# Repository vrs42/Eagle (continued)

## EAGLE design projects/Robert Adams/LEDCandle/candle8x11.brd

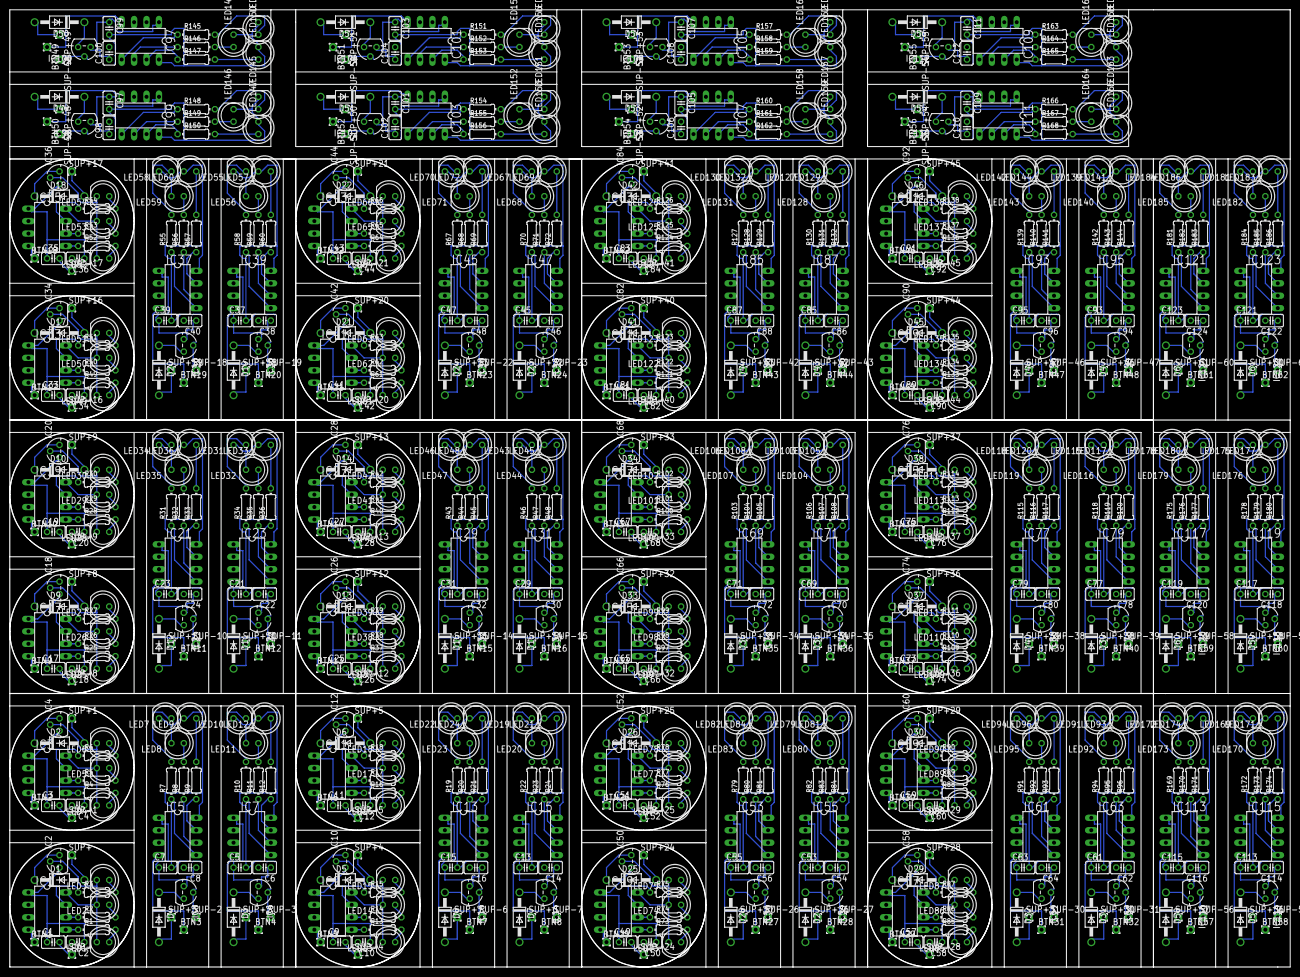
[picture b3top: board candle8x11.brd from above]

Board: 2 copper layers, 261.6 x 195.6 mm, 868 parts (0 on the bottom side), 596 nets.

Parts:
BTN1, BTN2, BTN3, BTN4, BTN5, BTN6, BTN7, BTN8, BTN9, BTN10, BTN11, BTN12, BTN13, BTN14, BTN15, BTN16, BTN17, BTN18, BTN19, BTN20, BTN21, BTN22, BTN23, BTN24, BTN25, BTN26, BTN27, BTN28, BTN29, BTN30, BTN31, BTN32, BTN33, BTN34, BTN35, BTN36, BTN37, BTN38, BTN39, BTN40, BTN41, BTN42, BTN43, BTN44, BTN45, BTN46, BTN47, BTN48, BTN49, BTN50, BTN51, BTN52, BTN53, BTN54, BTN55, BTN56, BTN57, BTN58, BTN59, BTN60, BTN61, BTN62: 1,6/0,8
C1, C2, C3, C4, C5, C6, C7, C8, C9, C10, C11, C12, C13, C14, C15, C16, C17, C18, C19, C20, C21, C22, C23, C24, C25, C26, C27, C28, C29, C30, C31, C32, C33, C34, C35, C36, C37, C38, C39, C40, C41, C42, C43, C44, C45, C46, C47, C48, C49, C50, C51, C52, C53, C54, C55, C56, C57, C58, C59, C60, C61, C62, C63, C64, C65, C66, C67, C68, C69, C70, C71, C72, C73, C74, C75, C76, C77, C78, C79, C80, C81, C82, C83, C84, C85, C86, C87, C88, C89, C90, C91, C92, C93, C94, C95, C96, C97, C98, C99, C100, C101, C102, C103, C104, C105, C106, C107, C108, C109, C110, C111, C112, C113, C114, C115, C116, C117, C118, C119, C120, C121, C122, C123, C124: C025-025X050
D1, D2, D3, D4, D5, D6, D7, D8, D9, D10, D11, D12, D13, D14, D15, D16, D17, D18, D19, D20, D21, D22, D23, D24, D25, D26, D27, D28, D29, D30, D31, D32, D33, D34, D35, D36, D37, D38, D39, D40, D41, D42, D43, D44, D45, D46, D47, D48, D49, D50, D51, D52, D53, D54, D55, D56, D57, D58, D59, D60, D61, D62: 1N4004; DO41-10
IC1, IC3, IC5, IC7, IC9, IC11, IC13, IC15, IC17, IC19, IC21, IC23, IC25, IC27, IC29, IC31, IC33, IC35, IC37, IC39, IC41, IC43, IC45, IC47, IC49, IC51, IC53, IC55, IC57, IC59, IC61, IC63, IC65, IC67, IC69, IC71, IC73, IC75, IC77, IC79, IC81, IC83, IC85, IC87, IC89, IC91, IC93, IC95, IC97, IC99, IC101, IC103, IC105, IC107, IC109, IC111, IC113, IC115, IC117, IC119, IC121, IC123: PIC12F629P; DIL8
IC2, IC4, IC6, IC8, IC10, IC12, IC14, IC16, IC18, IC20, IC22, IC24, IC26, IC28, IC30, IC32, IC34, IC36, IC38, IC40, IC42, IC44, IC46, IC48, IC50, IC52, IC54, IC56, IC58, IC60, IC62, IC64, IC66, IC68, IC70, IC72, IC74, IC76, IC78, IC80, IC82, IC84, IC86, IC88, IC90, IC92, IC94, IC96, IC98, IC100, IC102, IC104, IC106, IC108, IC110, IC112, IC114, IC116, IC118, IC120, IC122, IC124: 7805L; TO92
LED1, LED2, LED3, LED4, LED5, LED6, LED7, LED8, LED9, LED10, LED11, LED12, LED13, LED14, LED15, LED16, LED17, LED18, LED19, LED20, LED21, LED22, LED23, LED24, LED25, LED26, LED27, LED28, LED29, LED30, LED31, LED32, LED33, LED34, LED35, LED36, LED37, LED38, LED39, LED40, LED41, LED42, LED43, LED44, LED45, LED46, LED47, LED48, LED49, LED50, LED51, LED52, LED53, LED54, LED55, LED56, LED57, LED58, LED59, LED60, LED61, LED62, LED63, LED64, LED65, LED66, LED67, LED68, LED69, LED70, LED71, LED72, LED73, LED74, LED75, LED76, LED77, LED78, LED79, LED80, LED81, LED82, LED83, LED84, LED85, LED86, LED87, LED88, LED89, LED90, LED91, LED92, LED93, LED94, LED95, LED96, LED97, LED98, LED99, LED100, LED101, LED102, LED103, LED104, LED105, LED106, LED107, LED108, LED109, LED110, LED111, LED112, LED113, LED114, LED115, LED116, LED117, LED118, LED119, LED120, LED121, LED122, LED123, LED124, LED125, LED126, LED127, LED128, LED129, LED130, LED131, LED132, LED133, LED134, LED135, LED136, LED137, LED138, LED139, LED140, LED141, LED142, LED143, LED144, LED145, LED146, LED147, LED148, LED149, LED150, LED151, LED152, LED153, LED154, LED155, LED156, LED157, LED158, LED159, LED160, LED161, LED162, LED163, LED164, LED165, LED166, LED167, LED168, LED169, LED170, LED171, LED172, LED173, LED174, LED175, LED176, LED177, LED178, LED179, LED180, LED181, LED182, LED183, LED184, LED185, LED186: LED5MM
R1, R2, R3, R4, R5, R6, R7, R8, R9, R10, R11, R12, R13, R14, R15, R16, R17, R18, R19, R20, R21, R22, R23, R24, R25, R26, R27, R28, R29, R30, R31, R32, R33, R34, R35, R36, R37, R38, R39, R40, R41, R42, R43, R44, R45, R46, R47, R48, R49, R50, R51, R52, R53, R54, R55, R56, R57, R58, R59, R60, R61, R62, R63, R64, R65, R66, R67, R68, R69, R70, R71, R72, R73, R74, R75, R76, R77, R78, R79, R80, R81, R82, R83, R84, R85, R86, R87, R88, R89, R90, R91, R92, R93, R94, R95, R96, R97, R98, R99, R100, R101, R102, R103, R104, R105, R106, R107, R108, R109, R110, R111, R112, R113, R114, R115, R116, R117, R118, R119, R120, R121, R122, R123, R124, R125, R126, R127, R128, R129, R130, R131, R132, R133, R134, R135, R136, R137, R138, R139, R140, R141, R142, R143, R144, R145, R146, R147, R148, R149, R150, R151, R152, R153, R154, R155, R156, R157, R158, R159, R160, R161, R162, R163, R164, R165, R166, R167, R168, R169, R170, R171, R172, R173, R174, R175, R176, R177, R178, R179, R180, R181, R182, R183, R184, R185, R186: 0204/7
SUP+, SUP+1, SUP+2, SUP+3, SUP+4, SUP+5, SUP+6, SUP+7, SUP+8, SUP+9, SUP+10, SUP+11, SUP+12, SUP+13, SUP+14, SUP+15, SUP+16, SUP+17, SUP+18, SUP+19, SUP+20, SUP+21, SUP+22, SUP+23, SUP+24, SUP+25, SUP+26, SUP+27, SUP+28, SUP+29, SUP+30, SUP+31, SUP+32, SUP+33, SUP+34, SUP+35, SUP+36, SUP+37, SUP+38, SUP+39, SUP+40, SUP+41, SUP+42, SUP+43, SUP+44, SUP+45, SUP+46, SUP+47, SUP+48, SUP+49, SUP+50, SUP+51, SUP+52, SUP+53, SUP+54, SUP+55, SUP+56, SUP+57, SUP+58, SUP+59, SUP+60, SUP+61: 1,6/0,8
SUP-, SUP-1, SUP-2, SUP-3, SUP-4, SUP-5, SUP-6, SUP-7, SUP-8, SUP-9, SUP-10, SUP-11, SUP-12, SUP-13, SUP-14, SUP-15, SUP-16, SUP-17, SUP-18, SUP-19, SUP-20, SUP-21, SUP-22, SUP-23, SUP-24, SUP-25, SUP-26, SUP-27, SUP-28, SUP-29, SUP-30, SUP-31, SUP-32, SUP-33, SUP-34, SUP-35, SUP-36, SUP-37, SUP-38, SUP-39, SUP-40, SUP-41, SUP-42, SUP-43, SUP-44, SUP-45, SUP-46, SUP-47, SUP-48, SUP-49, SUP-50, SUP-51, SUP-52, SUP-53, SUP-54, SUP-55, SUP-56, SUP-57, SUP-58, SUP-59, SUP-60, SUP-61: 1,6/0,8

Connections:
GND: C1.2, C2.2, C3.2, C4.2, C5.2, C6.2, C7.2, C8.2, IC1.8, IC2.2, IC3.8, IC4.2, IC5.8, IC6.2, IC7.8, IC8.2, LED1.K, LED2.K, LED3.K, LED4.K, LED5.K, LED6.K, LED7.K, LED8.K, LED9.K, LED10.K, LED11.K, LED12.K, SUP-.1, SUP-1.1, SUP-2.1, SUP-3.1
GND1: C9.2, C10.2, C11.2, C12.2, C13.2, C14.2, C15.2, C16.2, IC9.8, IC10.2, IC11.8, IC12.2, IC13.8, IC14.2, IC15.8, IC16.2, LED13.K, LED14.K, LED15.K, LED16.K, LED17.K, LED18.K, LED19.K, LED20.K, LED21.K, LED22.K, LED23.K, LED24.K, SUP-4.1, SUP-5.1, SUP-6.1, SUP-7.1
GND2: C17.2, C18.2, C19.2, C20.2, C21.2, C22.2, C23.2, C24.2, IC17.8, IC18.2, IC19.8, IC20.2, IC21.8, IC22.2, IC23.8, IC24.2, LED25.K, LED26.K, LED27.K, LED28.K, LED29.K, LED30.K, LED31.K, LED32.K, LED33.K, LED34.K, LED35.K, LED36.K, SUP-8.1, SUP-9.1, SUP-10.1, SUP-11.1
GND3: C25.2, C26.2, C27.2, C28.2, C29.2, C30.2, C31.2, C32.2, IC25.8, IC26.2, IC27.8, IC28.2, IC29.8, IC30.2, IC31.8, IC32.2, LED37.K, LED38.K, LED39.K, LED40.K, LED41.K, LED42.K, LED43.K, LED44.K, LED45.K, LED46.K, LED47.K, LED48.K, SUP-12.1, SUP-13.1, SUP-14.1, SUP-15.1
GND4: C33.2, C34.2, C35.2, C36.2, C37.2, C38.2, C39.2, C40.2, IC33.8, IC34.2, IC35.8, IC36.2, IC37.8, IC38.2, IC39.8, IC40.2, LED49.K, LED50.K, LED51.K, LED52.K, LED53.K, LED54.K, LED55.K, LED56.K, LED57.K, LED58.K, LED59.K, LED60.K, SUP-16.1, SUP-17.1, SUP-18.1, SUP-19.1
GND5: C41.2, C42.2, C43.2, C44.2, C45.2, C46.2, C47.2, C48.2, IC41.8, IC42.2, IC43.8, IC44.2, IC45.8, IC46.2, IC47.8, IC48.2, LED61.K, LED62.K, LED63.K, LED64.K, LED65.K, LED66.K, LED67.K, LED68.K, LED69.K, LED70.K, LED71.K, LED72.K, SUP-20.1, SUP-21.1, SUP-22.1, SUP-23.1
GND6: C49.2, C50.2, C51.2, C52.2, C53.2, C54.2, C55.2, C56.2, IC49.8, IC50.2, IC51.8, IC52.2, IC53.8, IC54.2, IC55.8, IC56.2, LED73.K, LED74.K, LED75.K, LED76.K, LED77.K, LED78.K, LED79.K, LED80.K, LED81.K, LED82.K, LED83.K, LED84.K, SUP-24.1, SUP-25.1, SUP-26.1, SUP-27.1
GND7: C57.2, C58.2, C59.2, C60.2, C61.2, C62.2, C63.2, C64.2, IC57.8, IC58.2, IC59.8, IC60.2, IC61.8, IC62.2, IC63.8, IC64.2, LED85.K, LED86.K, LED87.K, LED88.K, LED89.K, LED90.K, LED91.K, LED92.K, LED93.K, LED94.K, LED95.K, LED96.K, SUP-28.1, SUP-29.1, SUP-30.1, SUP-31.1
GND8: C65.2, C66.2, C67.2, C68.2, C69.2, C70.2, C71.2, C72.2, IC65.8, IC66.2, IC67.8, IC68.2, IC69.8, IC70.2, IC71.8, IC72.2, LED97.K, LED98.K, LED99.K, LED100.K, LED101.K, LED102.K, LED103.K, LED104.K, LED105.K, LED106.K, LED107.K, LED108.K, SUP-32.1, SUP-33.1, SUP-34.1, SUP-35.1
GND9: C73.2, C74.2, C75.2, C76.2, C77.2, C78.2, C79.2, C80.2, IC73.8, IC74.2, IC75.8, IC76.2, IC77.8, IC78.2, IC79.8, IC80.2, LED109.K, LED110.K, LED111.K, LED112.K, LED113.K, LED114.K, LED115.K, LED116.K, LED117.K, LED118.K, LED119.K, LED120.K, SUP-36.1, SUP-37.1, SUP-38.1, SUP-39.1
GND10: C81.2, C82.2, C83.2, C84.2, C85.2, C86.2, C87.2, C88.2, IC81.8, IC82.2, IC83.8, IC84.2, IC85.8, IC86.2, IC87.8, IC88.2, LED121.K, LED122.K, LED123.K, LED124.K, LED125.K, LED126.K, LED127.K, LED128.K, LED129.K, LED130.K, LED131.K, LED132.K, SUP-40.1, SUP-41.1, SUP-42.1, SUP-43.1
GND11: C89.2, C90.2, C91.2, C92.2, C93.2, C94.2, C95.2, C96.2, IC89.8, IC90.2, IC91.8, IC92.2, IC93.8, IC94.2, IC95.8, IC96.2, LED133.K, LED134.K, LED135.K, LED136.K, LED137.K, LED138.K, LED139.K, LED140.K, LED141.K, LED142.K, LED143.K, LED144.K, SUP-44.1, SUP-45.1, SUP-46.1, SUP-47.1
GND12: C97.2, C98.2, C99.2, C100.2, IC97.8, IC98.2, IC99.8, IC100.2, LED145.K, LED146.K, LED147.K, LED148.K, LED149.K, LED150.K, SUP-48.1, SUP-49.1
GND13: C101.2, C102.2, C103.2, C104.2, IC101.8, IC102.2, IC103.8, IC104.2, LED151.K, LED152.K, LED153.K, LED154.K, LED155.K, LED156.K, SUP-50.1, SUP-51.1
GND14: C105.2, C106.2, C107.2, C108.2, IC105.8, IC106.2, IC107.8, IC108.2, LED157.K, LED158.K, LED159.K, LED160.K, LED161.K, LED162.K, SUP-52.1, SUP-53.1
GND15: C109.2, C110.2, C111.2, C112.2, IC109.8, IC110.2, IC111.8, IC112.2, LED163.K, LED164.K, LED165.K, LED166.K, LED167.K, LED168.K, SUP-54.1, SUP-55.1
GND16: C113.2, C114.2, C115.2, C116.2, IC113.8, IC114.2, IC115.8, IC116.2, LED169.K, LED170.K, LED171.K, LED172.K, LED173.K, LED174.K, SUP-56.1, SUP-57.1
GND17: C117.2, C118.2, C119.2, C120.2, IC117.8, IC118.2, IC119.8, IC120.2, LED175.K, LED176.K, LED177.K, LED178.K, LED179.K, LED180.K, SUP-58.1, SUP-59.1
GND18: C121.2, C122.2, C123.2, C124.2, IC121.8, IC122.2, IC123.8, IC124.2, LED181.K, LED182.K, LED183.K, LED184.K, LED185.K, LED186.K, SUP-60.1, SUP-61.1
unnamed: IC3.7, R6.1
unnamed: BTN1.1, IC1.4
unnamed: IC1.7, R3.1
unnamed: IC1.6, R2.1
unnamed: IC1.5, R1.1
unnamed: LED1.A, R1.2
unnamed: LED2.A, R2.2
unnamed: LED3.A, R3.2
unnamed: IC3.6, R5.1
unnamed: D1.C, IC2.3
unnamed: IC3.5, R4.1
unnamed: LED4.A, R4.2
unnamed: LED5.A, R5.2
unnamed: LED6.A, R6.2
unnamed: D2.C, IC4.3
unnamed: BTN2.1, IC3.4
unnamed: IC5.7, R9.1
unnamed: IC5.6, R8.1
unnamed: IC5.5, R7.1
unnamed: LED7.A, R7.2
unnamed: LED8.A, R8.2
unnamed: D3.C, IC6.3
unnamed: BTN3.1, IC5.4
unnamed: IC7.7, R12.1
unnamed: IC7.6, R11.1
unnamed: IC7.5, R10.1
unnamed: LED9.A, R9.2
unnamed: LED10.A, R10.2
unnamed: LED11.A, R11.2
unnamed: D4.C, IC8.3
unnamed: BTN4.1, IC7.4
unnamed: D1.A, SUP+.1
unnamed: LED12.A, R12.2
unnamed: D3.A, SUP+2.1
unnamed: D4.A, SUP+3.1
unnamed: D2.A, SUP+1.1
unnamed: IC9.7, R15.1
unnamed: IC9.6, R14.1
unnamed: IC9.5, R13.1
unnamed: D5.C, IC10.3
unnamed: BTN5.1, IC9.4
unnamed: IC11.7, R18.1
unnamed: IC11.6, R17.1
unnamed: IC11.5, R16.1
unnamed: D6.C, IC12.3
unnamed: BTN6.1, IC11.4
unnamed: IC13.7, R21.1
unnamed: IC13.6, R20.1
unnamed: IC13.5, R19.1
unnamed: D7.C, IC14.3
unnamed: BTN7.1, IC13.4
unnamed: IC15.7, R24.1
unnamed: IC15.6, R23.1
unnamed: IC15.5, R22.1
unnamed: D8.C, IC16.3
unnamed: BTN8.1, IC15.4
unnamed: D5.A, SUP+4.1
unnamed: LED13.A, R13.2
unnamed: LED14.A, R14.2
unnamed: LED15.A, R15.2
unnamed: LED16.A, R16.2
unnamed: LED17.A, R17.2
unnamed: LED18.A, R18.2
unnamed: LED19.A, R22.2
unnamed: LED20.A, R23.2
unnamed: LED21.A, R24.2
unnamed: LED22.A, R19.2
unnamed: LED23.A, R20.2
unnamed: LED24.A, R21.2
unnamed: D7.A, SUP+6.1
unnamed: D8.A, SUP+7.1
unnamed: D6.A, SUP+5.1
unnamed: IC17.7, R27.1
unnamed: IC17.6, R26.1
unnamed: IC17.5, R25.1
unnamed: D9.C, IC18.3
unnamed: BTN9.1, IC17.4
unnamed: IC19.7, R30.1
unnamed: IC19.6, R29.1
unnamed: IC19.5, R28.1
unnamed: D10.C, IC20.3
unnamed: BTN10.1, IC19.4
unnamed: IC21.7, R33.1
unnamed: IC21.6, R32.1
unnamed: IC21.5, R31.1
unnamed: D11.C, IC22.3
unnamed: BTN11.1, IC21.4
unnamed: IC23.7, R36.1
unnamed: IC23.6, R35.1
unnamed: IC23.5, R34.1
unnamed: D12.C, IC24.3
unnamed: BTN12.1, IC23.4
unnamed: D9.A, SUP+8.1
unnamed: LED25.A, R25.2
unnamed: LED26.A, R26.2
unnamed: LED27.A, R27.2
unnamed: LED28.A, R28.2
unnamed: LED29.A, R29.2
unnamed: LED30.A, R30.2
unnamed: LED31.A, R34.2
unnamed: LED32.A, R35.2
unnamed: LED33.A, R36.2
unnamed: LED34.A, R31.2
unnamed: LED35.A, R32.2
unnamed: LED36.A, R33.2
unnamed: D11.A, SUP+10.1
unnamed: D12.A, SUP+11.1
unnamed: D10.A, SUP+9.1
unnamed: IC25.7, R39.1
unnamed: IC25.6, R38.1
unnamed: IC25.5, R37.1
unnamed: D13.C, IC26.3
unnamed: BTN13.1, IC25.4
unnamed: IC27.7, R42.1
unnamed: IC27.6, R41.1
unnamed: IC27.5, R40.1
unnamed: D14.C, IC28.3
unnamed: BTN14.1, IC27.4
unnamed: IC29.7, R45.1
unnamed: IC29.6, R44.1
unnamed: IC29.5, R43.1
unnamed: D15.C, IC30.3
unnamed: BTN15.1, IC29.4
unnamed: IC31.7, R48.1
unnamed: IC31.6, R47.1
unnamed: IC31.5, R46.1
unnamed: D16.C, IC32.3
unnamed: BTN16.1, IC31.4
unnamed: D13.A, SUP+12.1
unnamed: LED37.A, R37.2
unnamed: LED38.A, R38.2
unnamed: LED39.A, R39.2
unnamed: LED40.A, R40.2
unnamed: LED41.A, R41.2
unnamed: LED42.A, R42.2
unnamed: LED43.A, R46.2
unnamed: LED44.A, R47.2
unnamed: LED45.A, R48.2
unnamed: LED46.A, R43.2
unnamed: LED47.A, R44.2
unnamed: LED48.A, R45.2
unnamed: D15.A, SUP+14.1
unnamed: D16.A, SUP+15.1
unnamed: D14.A, SUP+13.1
unnamed: IC33.7, R51.1
unnamed: IC33.6, R50.1
unnamed: IC33.5, R49.1
unnamed: D17.C, IC34.3
unnamed: BTN17.1, IC33.4
unnamed: IC35.7, R54.1
unnamed: IC35.6, R53.1
unnamed: IC35.5, R52.1
unnamed: D18.C, IC36.3
unnamed: BTN18.1, IC35.4
unnamed: IC37.7, R57.1
unnamed: IC37.6, R56.1
unnamed: IC37.5, R55.1
unnamed: D19.C, IC38.3
unnamed: BTN19.1, IC37.4
unnamed: IC39.7, R60.1
unnamed: IC39.6, R59.1
unnamed: IC39.5, R58.1
unnamed: D20.C, IC40.3
unnamed: BTN20.1, IC39.4
unnamed: D17.A, SUP+16.1
unnamed: LED49.A, R49.2
unnamed: LED50.A, R50.2
unnamed: LED51.A, R51.2
unnamed: LED52.A, R52.2
unnamed: LED53.A, R53.2
unnamed: LED54.A, R54.2
unnamed: LED55.A, R58.2
unnamed: LED56.A, R59.2
unnamed: LED57.A, R60.2
unnamed: LED58.A, R55.2
unnamed: LED59.A, R56.2
unnamed: LED60.A, R57.2
unnamed: D19.A, SUP+18.1
unnamed: D20.A, SUP+19.1
unnamed: D18.A, SUP+17.1
unnamed: IC41.7, R63.1
unnamed: IC41.6, R62.1
unnamed: IC41.5, R61.1
unnamed: D21.C, IC42.3
unnamed: BTN21.1, IC41.4
unnamed: IC43.7, R66.1
unnamed: IC43.6, R65.1
unnamed: IC43.5, R64.1
unnamed: D22.C, IC44.3
unnamed: BTN22.1, IC43.4
unnamed: IC45.7, R69.1
unnamed: IC45.6, R68.1
unnamed: IC45.5, R67.1
unnamed: D23.C, IC46.3
unnamed: BTN23.1, IC45.4
unnamed: IC47.7, R72.1
unnamed: IC47.6, R71.1
unnamed: IC47.5, R70.1
unnamed: D24.C, IC48.3
unnamed: BTN24.1, IC47.4
unnamed: D21.A, SUP+20.1
unnamed: LED61.A, R61.2
unnamed: LED62.A, R62.2
unnamed: LED63.A, R63.2
unnamed: LED64.A, R64.2
unnamed: LED65.A, R65.2
unnamed: LED66.A, R66.2
unnamed: LED67.A, R70.2
unnamed: LED68.A, R71.2
unnamed: LED69.A, R72.2
unnamed: LED70.A, R67.2
unnamed: LED71.A, R68.2
unnamed: LED72.A, R69.2
unnamed: D23.A, SUP+22.1
unnamed: D24.A, SUP+23.1
unnamed: D22.A, SUP+21.1
unnamed: IC49.7, R75.1
unnamed: IC49.6, R74.1
unnamed: IC49.5, R73.1
unnamed: D25.C, IC50.3
unnamed: BTN25.1, IC49.4
unnamed: IC51.7, R78.1
unnamed: IC51.6, R77.1
unnamed: IC51.5, R76.1
unnamed: D26.C, IC52.3
unnamed: BTN26.1, IC51.4
unnamed: IC53.7, R81.1
unnamed: IC53.6, R80.1
unnamed: IC53.5, R79.1
unnamed: D27.C, IC54.3
unnamed: BTN27.1, IC53.4
unnamed: IC55.7, R84.1
unnamed: IC55.6, R83.1
unnamed: IC55.5, R82.1
unnamed: D28.C, IC56.3
unnamed: BTN28.1, IC55.4
unnamed: D25.A, SUP+24.1
unnamed: LED73.A, R73.2
unnamed: LED74.A, R74.2
unnamed: LED75.A, R75.2
unnamed: LED76.A, R76.2
unnamed: LED77.A, R77.2
unnamed: LED78.A, R78.2
unnamed: LED79.A, R82.2
unnamed: LED80.A, R83.2
unnamed: LED81.A, R84.2
unnamed: LED82.A, R79.2
unnamed: LED83.A, R80.2
unnamed: LED84.A, R81.2
unnamed: D27.A, SUP+26.1
unnamed: D28.A, SUP+27.1
unnamed: D26.A, SUP+25.1
unnamed: IC57.7, R87.1
unnamed: IC57.6, R86.1
unnamed: IC57.5, R85.1
unnamed: D29.C, IC58.3
unnamed: BTN29.1, IC57.4
unnamed: IC59.7, R90.1
unnamed: IC59.6, R89.1
unnamed: IC59.5, R88.1
unnamed: D30.C, IC60.3
unnamed: BTN30.1, IC59.4
unnamed: IC61.7, R93.1
unnamed: IC61.6, R92.1
unnamed: IC61.5, R91.1
unnamed: D31.C, IC62.3
unnamed: BTN31.1, IC61.4
unnamed: IC63.7, R96.1
unnamed: IC63.6, R95.1
unnamed: IC63.5, R94.1
unnamed: D32.C, IC64.3
unnamed: BTN32.1, IC63.4
unnamed: D29.A, SUP+28.1
unnamed: LED85.A, R85.2
unnamed: LED86.A, R86.2
unnamed: LED87.A, R87.2
unnamed: LED88.A, R88.2
unnamed: LED89.A, R89.2
unnamed: LED90.A, R90.2
unnamed: LED91.A, R94.2
unnamed: LED92.A, R95.2
unnamed: LED93.A, R96.2
unnamed: LED94.A, R91.2
unnamed: LED95.A, R92.2
unnamed: LED96.A, R93.2
unnamed: D31.A, SUP+30.1
unnamed: D32.A, SUP+31.1
unnamed: D30.A, SUP+29.1
unnamed: IC65.7, R99.1
unnamed: IC65.6, R98.1
unnamed: IC65.5, R97.1
unnamed: D33.C, IC66.3
unnamed: BTN33.1, IC65.4
unnamed: IC67.7, R102.1
unnamed: IC67.6, R101.1
unnamed: IC67.5, R100.1
unnamed: D34.C, IC68.3
unnamed: BTN34.1, IC67.4
unnamed: IC69.7, R105.1
unnamed: IC69.6, R104.1
unnamed: IC69.5, R103.1
unnamed: D35.C, IC70.3
unnamed: BTN35.1, IC69.4
unnamed: IC71.7, R108.1
unnamed: IC71.6, R107.1
unnamed: IC71.5, R106.1
unnamed: D36.C, IC72.3
unnamed: BTN36.1, IC71.4
unnamed: D33.A, SUP+32.1
unnamed: LED97.A, R97.2
unnamed: LED98.A, R98.2
unnamed: LED99.A, R99.2
unnamed: LED100.A, R100.2
unnamed: LED101.A, R101.2
unnamed: LED102.A, R102.2
unnamed: LED103.A, R106.2
unnamed: LED104.A, R107.2
unnamed: LED105.A, R108.2
unnamed: LED106.A, R103.2
unnamed: LED107.A, R104.2
unnamed: LED108.A, R105.2
unnamed: D35.A, SUP+34.1
unnamed: D36.A, SUP+35.1
unnamed: D34.A, SUP+33.1
unnamed: IC73.7, R111.1
unnamed: IC73.6, R110.1
unnamed: IC73.5, R109.1
unnamed: D37.C, IC74.3
unnamed: BTN37.1, IC73.4
unnamed: IC75.7, R114.1
unnamed: IC75.6, R113.1
unnamed: IC75.5, R112.1
unnamed: D38.C, IC76.3
unnamed: BTN38.1, IC75.4
unnamed: IC77.7, R117.1
unnamed: IC77.6, R116.1
unnamed: IC77.5, R115.1
unnamed: D39.C, IC78.3
unnamed: BTN39.1, IC77.4
unnamed: IC79.7, R120.1
unnamed: IC79.6, R119.1
unnamed: IC79.5, R118.1
unnamed: D40.C, IC80.3
unnamed: BTN40.1, IC79.4
unnamed: D37.A, SUP+36.1
unnamed: LED109.A, R109.2
unnamed: LED110.A, R110.2
unnamed: LED111.A, R111.2
unnamed: LED112.A, R112.2
unnamed: LED113.A, R113.2
unnamed: LED114.A, R114.2
unnamed: LED115.A, R118.2
unnamed: LED116.A, R119.2
unnamed: LED117.A, R120.2
unnamed: LED118.A, R115.2
unnamed: LED119.A, R116.2
unnamed: LED120.A, R117.2
unnamed: D39.A, SUP+38.1
unnamed: D40.A, SUP+39.1
unnamed: D38.A, SUP+37.1
unnamed: IC81.7, R123.1
unnamed: IC81.6, R122.1
unnamed: IC81.5, R121.1
unnamed: D41.C, IC82.3
unnamed: BTN41.1, IC81.4
unnamed: IC83.7, R126.1
unnamed: IC83.6, R125.1
unnamed: IC83.5, R124.1
unnamed: D42.C, IC84.3
unnamed: BTN42.1, IC83.4
unnamed: IC85.7, R129.1
unnamed: IC85.6, R128.1
unnamed: IC85.5, R127.1
unnamed: D43.C, IC86.3
unnamed: BTN43.1, IC85.4
unnamed: IC87.7, R132.1
unnamed: IC87.6, R131.1
unnamed: IC87.5, R130.1
unnamed: D44.C, IC88.3
unnamed: BTN44.1, IC87.4
unnamed: D41.A, SUP+40.1
unnamed: LED121.A, R121.2
unnamed: LED122.A, R122.2
unnamed: LED123.A, R123.2
unnamed: LED124.A, R124.2
unnamed: LED125.A, R125.2
unnamed: LED126.A, R126.2
unnamed: LED127.A, R130.2
unnamed: LED128.A, R131.2
unnamed: LED129.A, R132.2
unnamed: LED130.A, R127.2
unnamed: LED131.A, R128.2
unnamed: LED132.A, R129.2
unnamed: D43.A, SUP+42.1
unnamed: D44.A, SUP+43.1
unnamed: D42.A, SUP+41.1
unnamed: IC89.7, R135.1
unnamed: IC89.6, R134.1
unnamed: IC89.5, R133.1
unnamed: D45.C, IC90.3
unnamed: BTN45.1, IC89.4
unnamed: IC91.7, R138.1
unnamed: IC91.6, R137.1
unnamed: IC91.5, R136.1
unnamed: D46.C, IC92.3
unnamed: BTN46.1, IC91.4
unnamed: IC93.7, R141.1
unnamed: IC93.6, R140.1
unnamed: IC93.5, R139.1
unnamed: D47.C, IC94.3
unnamed: BTN47.1, IC93.4
unnamed: IC95.7, R144.1
unnamed: IC95.6, R143.1
unnamed: IC95.5, R142.1
unnamed: D48.C, IC96.3
unnamed: BTN48.1, IC95.4
unnamed: D45.A, SUP+44.1
unnamed: LED133.A, R133.2
unnamed: LED134.A, R134.2
unnamed: LED135.A, R135.2
unnamed: LED136.A, R136.2
unnamed: LED137.A, R137.2
unnamed: LED138.A, R138.2
unnamed: LED139.A, R142.2
unnamed: LED140.A, R143.2
unnamed: LED141.A, R144.2
unnamed: LED142.A, R139.2
unnamed: LED143.A, R140.2
unnamed: LED144.A, R141.2
unnamed: D47.A, SUP+46.1
unnamed: D48.A, SUP+47.1
unnamed: D46.A, SUP+45.1
unnamed: IC97.7, R147.1
unnamed: IC97.6, R146.1
unnamed: IC97.5, R145.1
unnamed: D49.C, IC98.3
unnamed: BTN49.1, IC97.4
unnamed: IC99.7, R150.1
unnamed: IC99.6, R149.1
unnamed: IC99.5, R148.1
unnamed: D50.C, IC100.3
unnamed: BTN50.1, IC99.4
unnamed: LED145.A, R148.2
unnamed: LED146.A, R149.2
unnamed: LED147.A, R150.2
unnamed: LED148.A, R145.2
unnamed: LED149.A, R146.2
unnamed: LED150.A, R147.2
unnamed: D49.A, SUP+48.1
unnamed: D50.A, SUP+49.1
unnamed: IC101.7, R153.1
unnamed: IC101.6, R152.1
unnamed: IC101.5, R151.1
unnamed: D51.C, IC102.3
unnamed: BTN51.1, IC101.4
unnamed: IC103.7, R156.1
unnamed: IC103.6, R155.1
unnamed: IC103.5, R154.1
unnamed: D52.C, IC104.3
unnamed: BTN52.1, IC103.4
unnamed: LED151.A, R154.2
unnamed: LED152.A, R155.2
unnamed: LED153.A, R156.2
unnamed: LED154.A, R151.2
unnamed: LED155.A, R152.2
unnamed: LED156.A, R153.2
unnamed: D51.A, SUP+50.1
unnamed: D52.A, SUP+51.1
unnamed: IC105.7, R159.1
unnamed: IC105.6, R158.1
unnamed: IC105.5, R157.1
unnamed: D53.C, IC106.3
unnamed: BTN53.1, IC105.4
unnamed: IC107.7, R162.1
unnamed: IC107.6, R161.1
unnamed: IC107.5, R160.1
unnamed: D54.C, IC108.3
unnamed: BTN54.1, IC107.4
unnamed: LED157.A, R160.2
unnamed: LED158.A, R161.2
unnamed: LED159.A, R162.2
unnamed: LED160.A, R157.2
unnamed: LED161.A, R158.2
unnamed: LED162.A, R159.2
unnamed: D53.A, SUP+52.1
unnamed: D54.A, SUP+53.1
unnamed: IC109.7, R165.1
unnamed: IC109.6, R164.1
unnamed: IC109.5, R163.1
unnamed: D55.C, IC110.3
unnamed: BTN55.1, IC109.4
unnamed: IC111.7, R168.1
unnamed: IC111.6, R167.1
unnamed: IC111.5, R166.1
unnamed: D56.C, IC112.3
unnamed: BTN56.1, IC111.4
unnamed: LED163.A, R166.2
unnamed: LED164.A, R167.2
unnamed: LED165.A, R168.2
unnamed: LED166.A, R163.2
unnamed: LED167.A, R164.2
unnamed: LED168.A, R165.2
unnamed: D55.A, SUP+54.1
unnamed: D56.A, SUP+55.1
unnamed: IC113.7, R171.1
unnamed: IC113.6, R170.1
unnamed: IC113.5, R169.1
unnamed: D57.C, IC114.3
unnamed: BTN57.1, IC113.4
unnamed: IC115.7, R174.1
unnamed: IC115.6, R173.1
unnamed: IC115.5, R172.1
unnamed: D58.C, IC116.3
unnamed: BTN58.1, IC115.4
unnamed: LED169.A, R172.2
unnamed: LED170.A, R173.2
unnamed: LED171.A, R174.2
unnamed: LED172.A, R169.2
unnamed: LED173.A, R170.2
unnamed: LED174.A, R171.2
unnamed: D57.A, SUP+56.1
unnamed: D58.A, SUP+57.1
unnamed: IC117.7, R177.1
unnamed: IC117.6, R176.1
unnamed: IC117.5, R175.1
unnamed: D59.C, IC118.3
unnamed: BTN59.1, IC117.4
unnamed: IC119.7, R180.1
unnamed: IC119.6, R179.1
unnamed: IC119.5, R178.1
unnamed: D60.C, IC120.3
unnamed: BTN60.1, IC119.4
unnamed: LED175.A, R178.2
unnamed: LED176.A, R179.2
unnamed: LED177.A, R180.2
unnamed: LED178.A, R175.2
unnamed: LED179.A, R176.2
unnamed: LED180.A, R177.2
unnamed: D59.A, SUP+58.1
unnamed: D60.A, SUP+59.1
unnamed: IC121.7, R183.1
unnamed: IC121.6, R182.1
unnamed: IC121.5, R181.1
unnamed: D61.C, IC122.3
unnamed: BTN61.1, IC121.4
unnamed: IC123.7, R186.1
unnamed: IC123.6, R185.1
unnamed: IC123.5, R184.1
unnamed: D62.C, IC124.3
unnamed: BTN62.1, IC123.4
unnamed: LED181.A, R184.2
unnamed: LED182.A, R185.2
unnamed: LED183.A, R186.2
unnamed: LED184.A, R181.2
unnamed: LED185.A, R182.2
unnamed: LED186.A, R183.2
unnamed: D61.A, SUP+60.1
unnamed: D62.A, SUP+61.1
VCC: C1.1, C2.1, C3.1, C4.1, C5.1, C6.1, C7.1, C8.1, IC1.1, IC2.1, IC3.1, IC4.1, IC5.1, IC6.1, IC7.1, IC8.1
VCC1: C9.1, C10.1, C11.1, C12.1, C13.1, C14.1, C15.1, C16.1, IC9.1, IC10.1, IC11.1, IC12.1, IC13.1, IC14.1, IC15.1, IC16.1
VCC2: C17.1, C18.1, C19.1, C20.1, C21.1, C22.1, C23.1, C24.1, IC17.1, IC18.1, IC19.1, IC20.1, IC21.1, IC22.1, IC23.1, IC24.1
VCC3: C25.1, C26.1, C27.1, C28.1, C29.1, C30.1, C31.1, C32.1, IC25.1, IC26.1, IC27.1, IC28.1, IC29.1, IC30.1, IC31.1, IC32.1
VCC4: C33.1, C34.1, C35.1, C36.1, C37.1, C38.1, C39.1, C40.1, IC33.1, IC34.1, IC35.1, IC36.1, IC37.1, IC38.1, IC39.1, IC40.1
VCC5: C41.1, C42.1, C43.1, C44.1, C45.1, C46.1, C47.1, C48.1, IC41.1, IC42.1, IC43.1, IC44.1, IC45.1, IC46.1, IC47.1, IC48.1
VCC6: C49.1, C50.1, C51.1, C52.1, C53.1, C54.1, C55.1, C56.1, IC49.1, IC50.1, IC51.1, IC52.1, IC53.1, IC54.1, IC55.1, IC56.1
VCC7: C57.1, C58.1, C59.1, C60.1, C61.1, C62.1, C63.1, C64.1, IC57.1, IC58.1, IC59.1, IC60.1, IC61.1, IC62.1, IC63.1, IC64.1
VCC8: C65.1, C66.1, C67.1, C68.1, C69.1, C70.1, C71.1, C72.1, IC65.1, IC66.1, IC67.1, IC68.1, IC69.1, IC70.1, IC71.1, IC72.1
VCC9: C73.1, C74.1, C75.1, C76.1, C77.1, C78.1, C79.1, C80.1, IC73.1, IC74.1, IC75.1, IC76.1, IC77.1, IC78.1, IC79.1, IC80.1
VCC10: C81.1, C82.1, C83.1, C84.1, C85.1, C86.1, C87.1, C88.1, IC81.1, IC82.1, IC83.1, IC84.1, IC85.1, IC86.1, IC87.1, IC88.1
VCC11: C89.1, C90.1, C91.1, C92.1, C93.1, C94.1, C95.1, C96.1, IC89.1, IC90.1, IC91.1, IC92.1, IC93.1, IC94.1, IC95.1, IC96.1
VCC12: C97.1, C98.1, C99.1, C100.1, IC97.1, IC98.1, IC99.1, IC100.1
VCC13: C101.1, C102.1, C103.1, C104.1, IC101.1, IC102.1, IC103.1, IC104.1
VCC14: C105.1, C106.1, C107.1, C108.1, IC105.1, IC106.1, IC107.1, IC108.1
VCC15: C109.1, C110.1, C111.1, C112.1, IC109.1, IC110.1, IC111.1, IC112.1
VCC16: C113.1, C114.1, C115.1, C116.1, IC113.1, IC114.1, IC115.1, IC116.1
VCC17: C117.1, C118.1, C119.1, C120.1, IC117.1, IC118.1, IC119.1, IC120.1
VCC18: C121.1, C122.1, C123.1, C124.1, IC121.1, IC122.1, IC123.1, IC124.1

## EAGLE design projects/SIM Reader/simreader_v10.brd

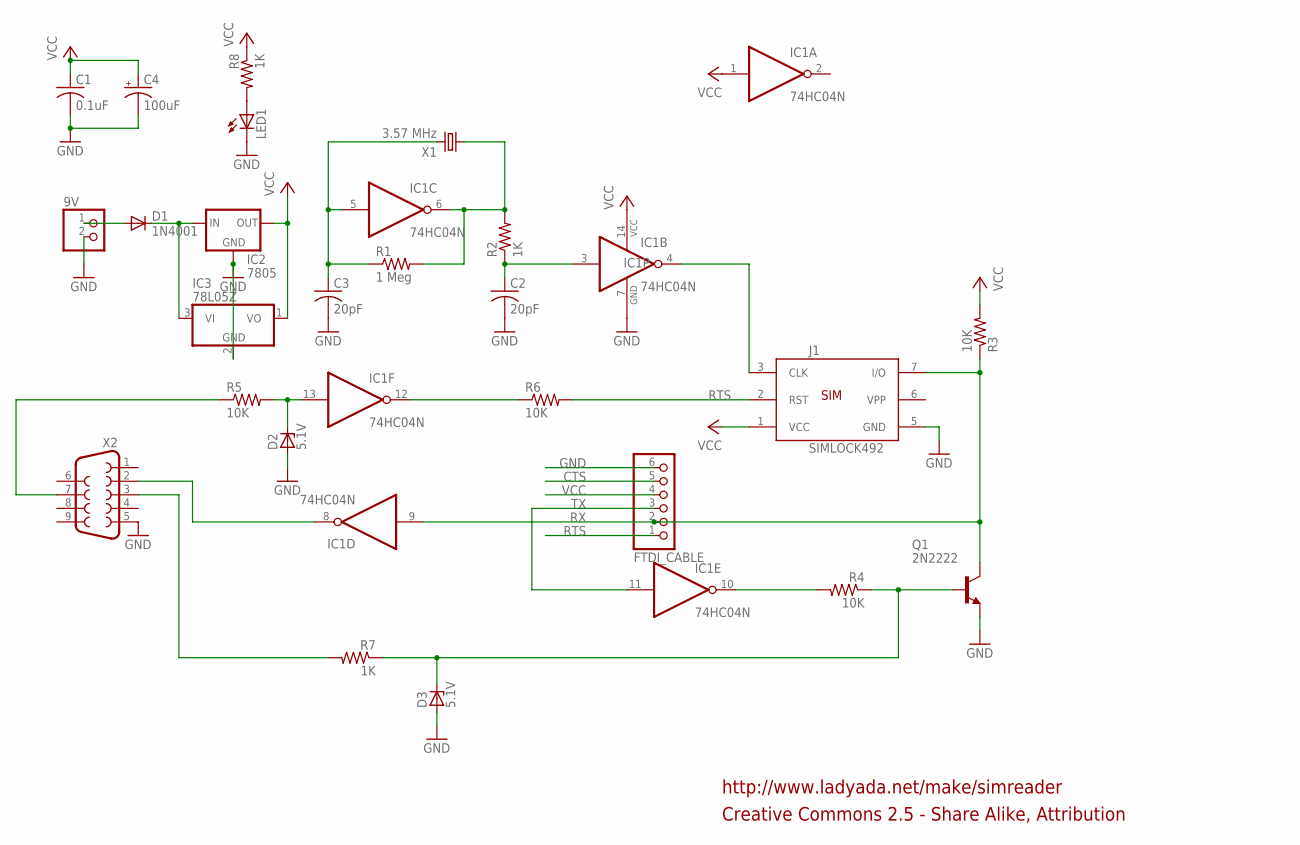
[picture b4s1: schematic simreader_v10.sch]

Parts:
9V: PINHD-1X2; 1X02
C1: 0.1uF; C025-025X050
C2, C3: 20pF; C025-025X050
C4: 100uF; E2,5-5
D1: 1N4001; DO41-10
D2, D3: 5.1V; DO35Z10
FTDI_CABLE: PINHD-1X6; 1X06
IC1: 74HC04N; DIL14
IC2: 7805; 78XXS
IC3: 78L05Z; TO92
J1: SIMLOCK492; 5002
LED1: LED3MM
Q1: 2N2222; TO92-EBC
R1: 1 Meg; 0207/10
R2, R7, R8: 1K; 0207/10
R3, R4, R5, R6: 10K; 0207/10
X1: 3.57 MHz; HC49
X2: F09D

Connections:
CTS: FTDI_CABLE.5
GND: 9V.2, C1.2, C2.2, C3.2, C4.-, D2.A, D3.A, FTDI_CABLE.6, IC1.7 (GND), IC2.GND, IC3.2 (GND), J1.5 (GND), LED1.K (C), Q1.E, X2.5
unnamed: C3.1, IC1.5 (I), R1.1, X1.2
unnamed: IC1.6 (O), R1.2, R2.2, X1.1
unnamed: C2.1, IC1.3 (I), R2.1
unnamed: IC1.10 (O), R4.2
unnamed: IC1.4 (O), J1.3 (CLK)
unnamed: D3.C, Q1.B, R4.1, R7.1
unnamed: D1.C, IC2.IN, IC3.3 (VI)
unnamed: IC1.8 (O), X2.2
unnamed: R5.1, X2.7
unnamed: D2.C, IC1.13 (I), R5.2
unnamed: IC1.12 (O), R6.1
unnamed: R7.2, X2.3
unnamed: LED1.A, R8.2
unnamed: 9V.1, D1.A
RTS: FTDI_CABLE.1, J1.2 (RST), R6.2
RX: FTDI_CABLE.2, IC1.9 (I), J1.7 (I/O), Q1.C, R3.1
TX: FTDI_CABLE.3, IC1.11 (I)
VCC: C1.1, C4.+, FTDI_CABLE.4, IC1.1 (I), IC1.14 (VCC), IC2.OUT, IC3.1 (VO), J1.1 (VCC), R3.2, R8.1

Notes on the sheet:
Creative Commons 2.5 - Share Alike, Attribution
http://www.ladyada.net/make/simreader

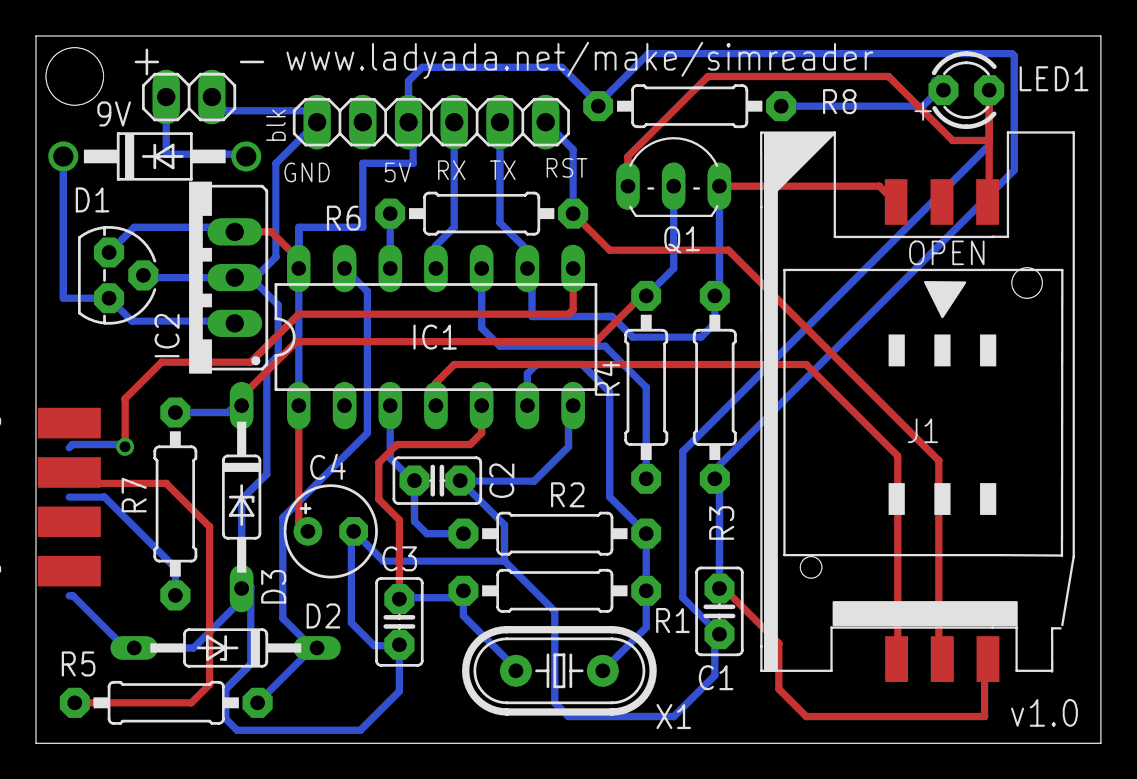
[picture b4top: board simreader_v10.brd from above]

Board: 2 copper layers, 59.2 x 39.3 mm, 25 parts (1 on the bottom side), 19 nets.

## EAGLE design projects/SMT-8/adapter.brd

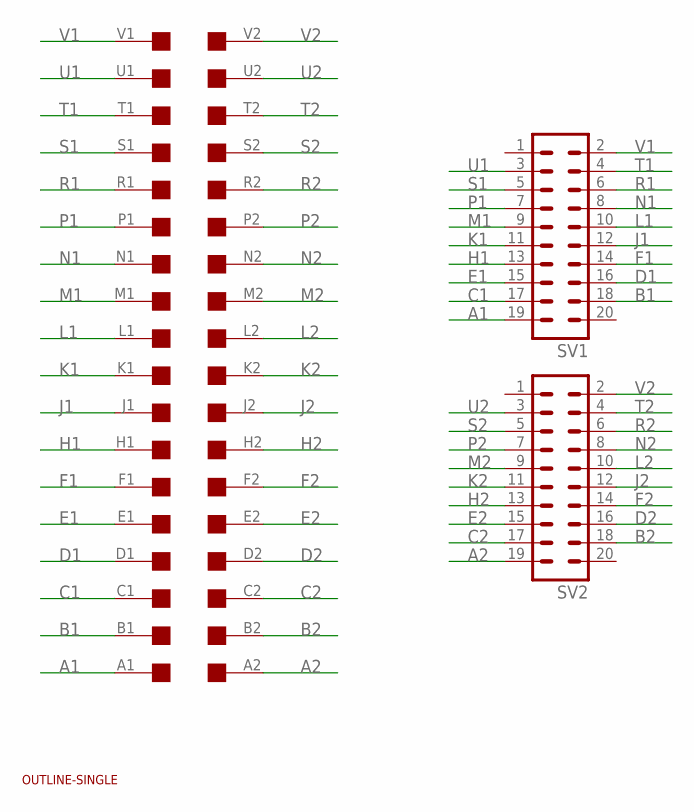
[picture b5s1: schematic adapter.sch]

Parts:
SV1, SV2: MA10-2W
U$1: OUTLINE-SINGLE; SINGLE
U$2: SINGLE; EDGE-CON2

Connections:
A1: SV1.19, U$2.A1
A2: SV2.19, U$2.A2
B1: SV1.18, U$2.B1
B2: SV2.18, U$2.B2
C1: SV1.17, U$2.C1
C2: SV2.17, U$2.C2
D1: SV1.16, U$2.D1
D2: SV2.16, U$2.D2
E1: SV1.15, U$2.E1
E2: SV2.15, U$2.E2
F1: SV1.14, U$2.F1
F2: SV2.14, U$2.F2
H1: SV1.13, U$2.H1
H2: SV2.13, U$2.H2
J1: SV1.12, U$2.J1
J2: SV2.12, U$2.J2
K1: SV1.11, U$2.K1
K2: SV2.11, U$2.K2
L1: SV1.10, U$2.L1
L2: SV2.10, U$2.L2
M1: SV1.9, U$2.M1
M2: SV2.9, U$2.M2
N1: SV1.8, U$2.N1
N2: SV2.8, U$2.N2
P1: SV1.7, U$2.P1
P2: SV2.7, U$2.P2
R1: SV1.6, U$2.R1
R2: SV2.6, U$2.R2
S1: SV1.5, U$2.S1
S2: SV2.5, U$2.S2
T1: SV1.4, U$2.T1
T2: SV2.4, U$2.T2
U1: SV1.3, U$2.U1
U2: SV2.3, U$2.U2
V1: SV1.2, U$2.V1
V2: SV2.2, U$2.V2

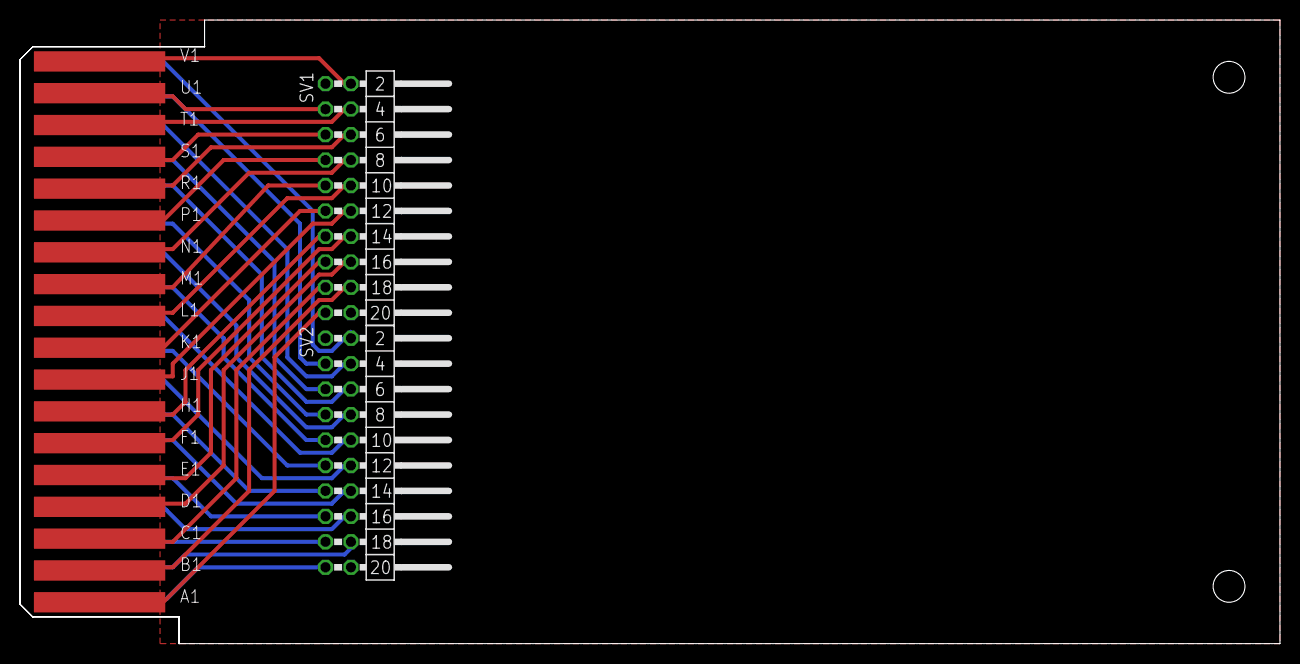
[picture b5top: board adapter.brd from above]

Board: 2 copper layers, 125.7 x 62.2 mm, 4 parts (0 on the bottom side), 36 nets.
